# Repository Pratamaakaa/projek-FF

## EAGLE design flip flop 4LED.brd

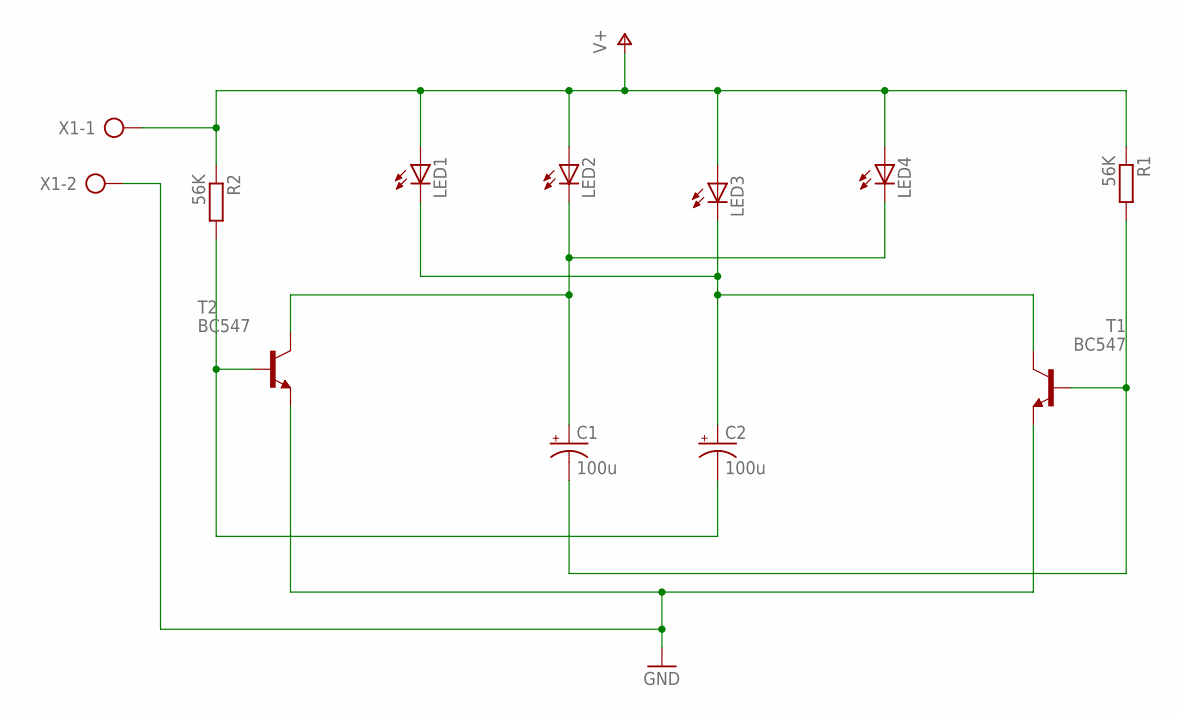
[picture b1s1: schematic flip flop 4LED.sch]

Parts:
C1, C2: 100u; E5-5
LED1, LED2, LED3, LED4: LED_ELD260; LED_LD260
R1, R2: 56K; 0309/12
T1, T2: BC547; TO92
X1: AK500/2-H

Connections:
GND: T1.1 (E), T2.1 (E), X1.2
unnamed: C2.+, LED1.K (C), LED3.K (C), T1.3 (C)
unnamed: C1.-, R1.2, T1.2 (B)
unnamed: C1.+, LED2.K (C), LED4.K (C), T2.3 (C)
unnamed: C2.-, R2.2, T2.2 (B)
V+: LED1.A, LED2.A, LED3.A, LED4.A, R1.1, R2.1, X1.1

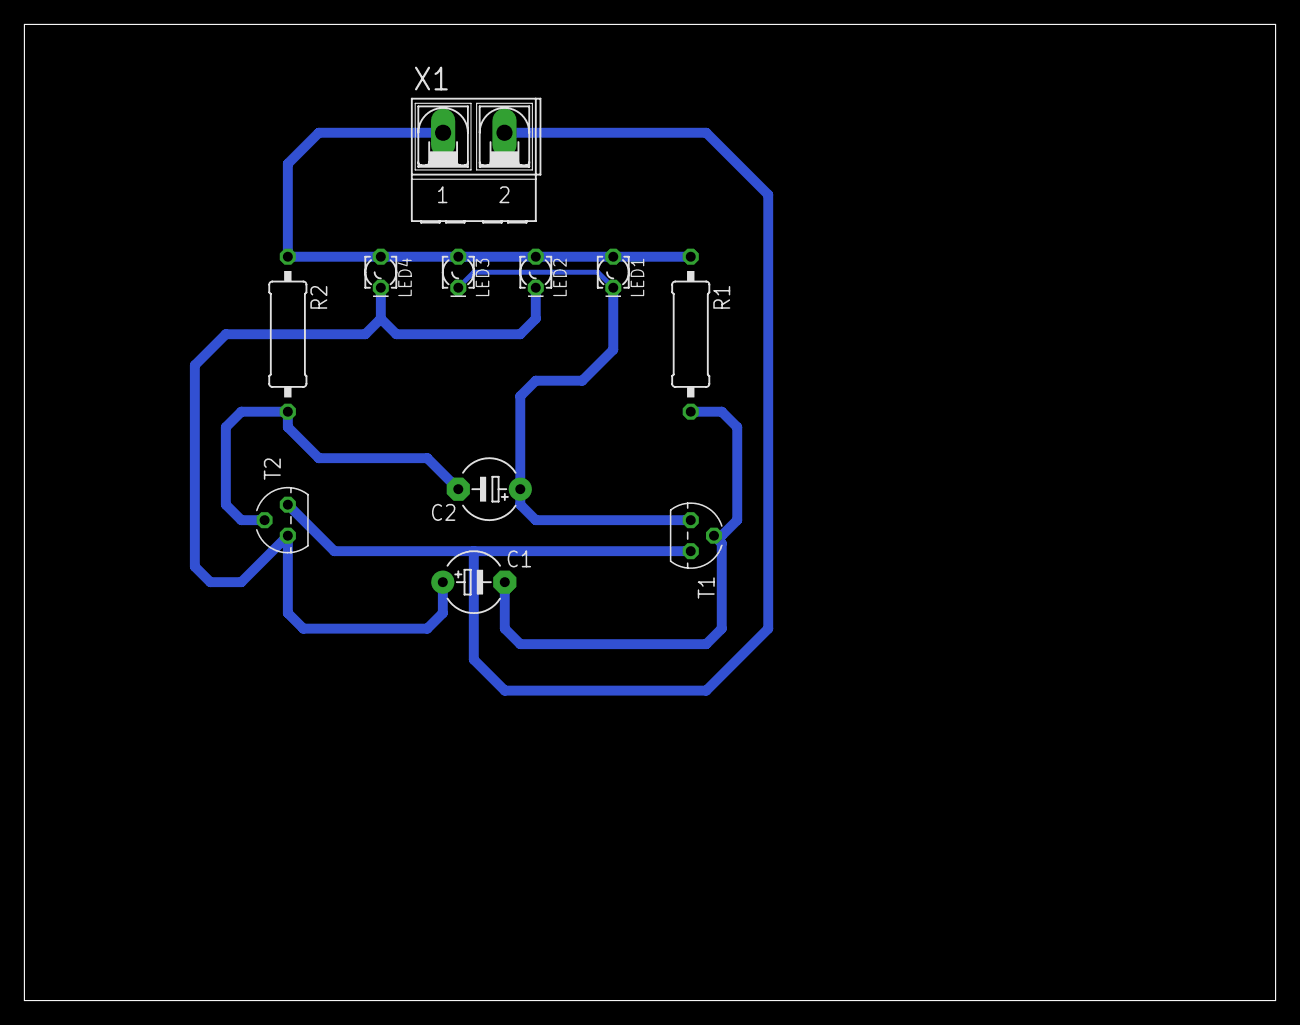
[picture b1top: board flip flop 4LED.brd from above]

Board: 2 copper layers, 102.5 x 80.0 mm, 11 parts (0 on the bottom side), 6 nets.

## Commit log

2025-01-14 projek FF
